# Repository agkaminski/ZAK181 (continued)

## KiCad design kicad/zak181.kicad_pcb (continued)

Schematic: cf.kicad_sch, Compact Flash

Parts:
C73: 100p; C_Disc_D5.0mm_W2.5mm_P2.50mm
D3: ACTIVITY; LED_D5.0mm
J3: Compact Flash; Conn_CF_N7E50-Q516XX-40
R19: 1K; R_Axial_DIN0207_L6.3mm_D2.5mm_P7.62mm_Horizontal
R20: 100R; R_Axial_DIN0207_L6.3mm_D2.5mm_P7.62mm_Horizontal
RN3: 1K; R_Array_SIP5

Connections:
/A0: J3.20 (A0); also elsewhere on the board
/A1: J3.19 (A1); also elsewhere on the board
/A2: J3.18 (A2); also elsewhere on the board
/D0: J3.21 (D0); also elsewhere on the board
/D1: J3.22 (D1); also elsewhere on the board
/D2: J3.23 (D2); also elsewhere on the board
/D3: J3.2 (D3); also elsewhere on the board
/D4: J3.3 (D4); also elsewhere on the board
/D5: J3.4 (D5); also elsewhere on the board
/D6: J3.5 (D6); also elsewhere on the board
/D7: J3.6 (D7); also elsewhere on the board
/cf/IRQ: J3.37 (INTRQ); also elsewhere on the board
/cf/~CS: J3.7 (~CS0); also elsewhere on the board
/cf/~RD: R20.2; also elsewhere on the board
/cf/~WR: J3.35 (~IOWR); also elsewhere on the board
/cpu/~RST: J3.41 (~RESET); also elsewhere on the board
GND: C73.2, J3.1 (GND), J3.8 (A10), J3.9 (~ATASEL), J3.10 (A9), J3.11 (A8), J3.12 (A7), J3.14 (A6), J3.15 (A5), J3.16 (A4), J3.17 (A3), J3.39 (~CSEL), J3.50 (GND); also elsewhere on the board
unnamed: D3.2 (A), R19.1
unnamed: D3.1 (K), J3.45 (~DASP)
unnamed: J3.32 (~CS1), RN3.5 (R4)
unnamed: C73.1, J3.34 (~IORD), R20.1
unnamed: J3.46 (~PDIAG), RN3.2 (R1)
unnamed: J3.44 (~REG), RN3.4 (R3)
unnamed: J3.36 (~WE), RN3.3 (R2)
VCC: J3.13 (VCC), J3.38 (VCC), R19.2, RN3.1 (common); also elsewhere on the board

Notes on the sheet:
Regarding CF slot footprint: Market is a proper mess. These cards seem to be obsolete and everything is hard to aquire. Footprint used fits somewhat avaiable CF-50P - normal order, not reversed! Card has to be label up when inserted!

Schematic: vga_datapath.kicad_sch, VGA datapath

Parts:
C4, C5, C6, C7, C8, C9, C10, C11, C12, C13: 100n; C_Disc_D5.0mm_W2.5mm_P2.50mm
Q3, Q4, Q5: BC547; TO-92
R6, R11, R14: 390R; R_Axial_DIN0207_L6.3mm_D2.5mm_P7.62mm_Horizontal
R7, R8, R9, R10, R12, R13: 3K3; R_Axial_DIN0207_L6.3mm_D2.5mm_P7.62mm_Horizontal
U21, U30: 74HC377; DIP-20_W7.62mm
U23: 27C64; DIP-28_W15.24mm
U24: 74HC166; DIP-16_W7.62mm
U27: 62256; DIP-28_W15.24mm
U32: 74HC157; DIP-16_W7.62mm

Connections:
/sound/ROMSEL0: U23.23 (A11); also elsewhere on the board
/sound/ROMSEL1: U23.2 (A12); also elsewhere on the board
/vga/BLANK: U32.15 (E); also elsewhere on the board
/vga/PCLK: U21.11 (CP), U24.7 (Clk), U30.11 (CP); also elsewhere on the board
/vga/VA0: U27.10 (A0); also elsewhere on the board
/vga/VA1: U27.9 (A1); also elsewhere on the board
/vga/VA2: U27.8 (A2); also elsewhere on the board
/vga/VA3: U27.7 (A3); also elsewhere on the board
/vga/VA4: U27.6 (A4); also elsewhere on the board
/vga/VA5: U27.5 (A5); also elsewhere on the board
/vga/VA6: U27.4 (A6); also elsewhere on the board
/vga/VA7: U27.3 (A7); also elsewhere on the board
/vga/VA8: U27.25 (A8); also elsewhere on the board
/vga/VA9: U27.24 (A9); also elsewhere on the board
/vga/VA10: U27.21 (A10); also elsewhere on the board
/vga/VA11: U27.23 (A11); also elsewhere on the board
/vga/VA12: U27.2 (A12); also elsewhere on the board
/vga/VA13: U27.26 (A13); also elsewhere on the board
/vga/VD0: U21.3 (D0), U27.11 (Q0), U30.3 (D0); also elsewhere on the board
/vga/VD1: U21.4 (D1), U27.12 (Q1), U30.4 (D1); also elsewhere on the board
/vga/VD2: U21.7 (D2), U27.13 (Q2), U30.7 (D2); also elsewhere on the board
/vga/VD3: U21.8 (D3), U27.15 (Q3), U30.8 (D3); also elsewhere on the board
/vga/VD4: U21.13 (D4), U27.16 (Q4), U30.13 (D4); also elsewhere on the board
/vga/VD5: U21.14 (D5), U27.17 (Q5), U30.14 (D5); also elsewhere on the board
/vga/VD6: U21.17 (D6), U27.18 (Q6), U30.17 (D6); also elsewhere on the board
/vga/VD7: U21.18 (D7), U27.19 (Q7), U30.18 (D7); also elsewhere on the board
/vga/vga_datapath/BLUE: R14.2; also elsewhere on the board
/vga/vga_datapath/CROW0: U23.10 (A0); also elsewhere on the board
/vga/vga_datapath/CROW1: U23.9 (A1); also elsewhere on the board
/vga/vga_datapath/CROW2: U23.8 (A2); also elsewhere on the board
/vga/vga_datapath/GREEN: R11.2; also elsewhere on the board
/vga/vga_datapath/RED: R6.2; also elsewhere on the board
/vga/~CLOAD: U30.1 (~E); also elsewhere on the board
/vga/~PLOAD: U21.1 (~E); also elsewhere on the board
/vga/~SHLOAD: U24.15 (PE); also elsewhere on the board
/vga/~VOE: U27.22 (~OE); also elsewhere on the board
/vga/~VWE: U27.27 (~WE); also elsewhere on the board
GND: C4.2, C5.2, C6.2, C7.2, C8.2, C9.2, C10.2, C11.2, C12.2, C13.2, U21.10 (GND), U23.14 (GND), U23.20 (~CE), U23.22 (~OE), U24.1 (Ds), U24.6 (CE), U24.8 (GND), U27.1 (A14), U27.14 (GND), U27.20 (~CS), U30.10 (GND), U32.8 (GND); also elsewhere on the board
unnamed: Q3.2 (B), R7.2, R8.2
unnamed: Q3.3 (E), R6.1
unnamed: Q4.2 (B), R9.2, R10.2
unnamed: Q4.3 (E), R11.1
unnamed: Q5.2 (B), R12.2, R13.2
unnamed: Q5.3 (E), R14.1
unnamed: U21.2 (Q0), U23.7 (A3)
unnamed: U21.5 (Q1), U23.6 (A4)
unnamed: U21.6 (Q2), U23.5 (A5)
unnamed: U21.9 (Q3), U23.4 (A6)
unnamed: U21.12 (Q4), U23.3 (A7)
unnamed: U21.15 (Q5), U23.25 (A8)
unnamed: U21.16 (Q6), U23.24 (A9)
unnamed: U21.19 (Q7), U23.21 (A10)
unnamed: U23.11 (D0), U24.2 (A)
unnamed: U23.12 (D1), U24.3 (B)
unnamed: U23.13 (D2), U24.4 (C)
unnamed: U23.15 (D3), U24.5 (D)
unnamed: U23.16 (D4), U24.10 (E)
unnamed: U23.17 (D5), U24.11 (F)
unnamed: U23.18 (D6), U24.12 (G)
unnamed: U23.19 (D7), U24.14 (H)
unnamed: U24.13 (Qh), U32.1 (S)
unnamed: U30.2 (Q0), U32.2 (I0a)
unnamed: U30.5 (Q1), U32.5 (I0b)
unnamed: U30.6 (Q2), U32.11 (I0c)
unnamed: U30.9 (Q3), U32.14 (I0d)
unnamed: U30.12 (Q4), U32.3 (I1a)
unnamed: U30.15 (Q5), U32.6 (I1b)
unnamed: U30.16 (Q6), U32.10 (I1c)
unnamed: U30.19 (Q7), U32.13 (I1d)
unnamed: R7.1, U32.4 (Za)
unnamed: R9.1, U32.7 (Zb)
unnamed: R12.1, U32.9 (Zc)
unnamed: R8.1, R10.1, R13.1, U32.12 (Zd)
VCC: C4.1, C5.1, C6.1, C7.1, C8.1, C9.1, C10.1, C11.1, C12.1, C13.1, Q3.1 (C), Q4.1 (C), Q5.1 (C), U21.20 (VCC), U23.1 (VPP), U23.27 (~PGM), U23.28 (VCC), U24.9 (Clr), U24.16 (VCC), U27.28 (VCC), U30.20 (VCC), U32.16 (VCC); also elsewhere on the board

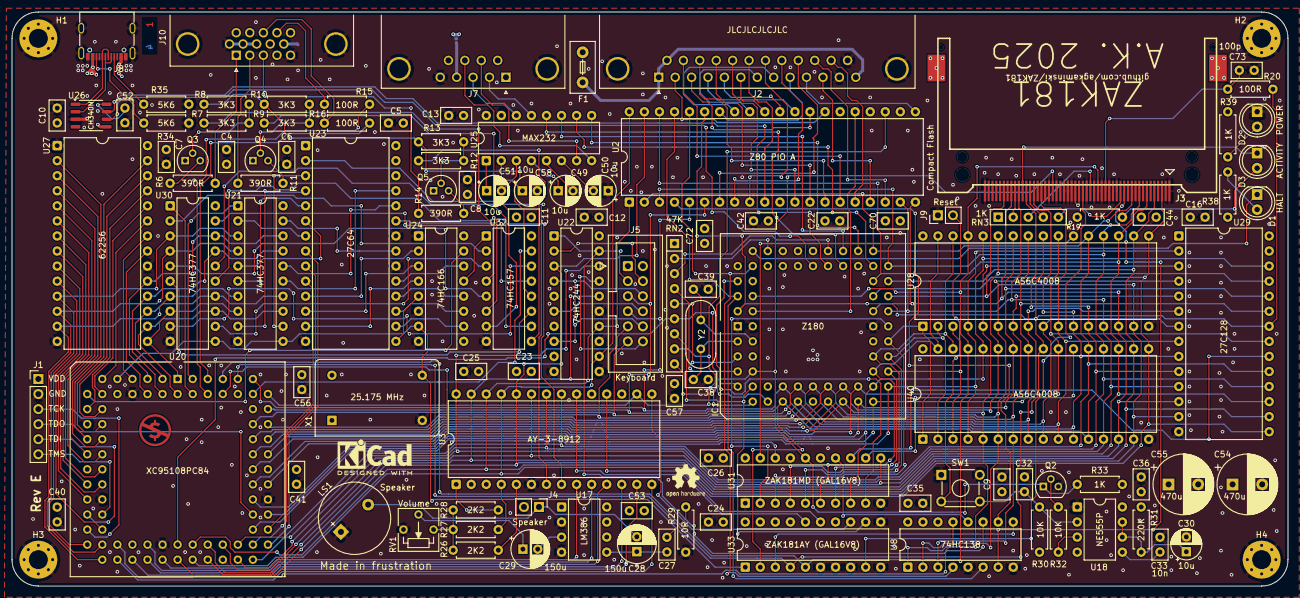
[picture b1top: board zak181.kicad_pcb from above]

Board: 4 copper layers, 215.3 x 96.8 mm, 118 parts (1 on the bottom side), 219 nets.

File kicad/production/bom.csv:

Designator,Footprint,Quantity,Value,LCSC Part #
"C10, C11, C12, C13, C16, C22, C23, C24, C25, C26, C32, C35, C36, C4, C40, C41, C42, C44, C5, C52, C53, C56, C57, C6, C7, C70, C72, C8, C9",C_Disc_D5.0mm_W2.5mm_P2.50mm,29,100n,
C27,C_Disc_D5.0mm_W2.5mm_P2.50mm,1,47n,
"C28, C29",CP_Radial_D6.3mm_P2.50mm,2,150u,
"C30, C49, C50, C51, C58",CP_Radial_D5.0mm_P2.50mm,5,10u,
C33,C_Disc_D5.0mm_W2.5mm_P2.50mm,1,10n,
"C38, C39",C_Disc_D5.0mm_W2.5mm_P2.50mm,2,22p,
"C54, C55",CP_Radial_D10.0mm_P5.00mm,2,470u,
C73,C_Disc_D5.0mm_W2.5mm_P2.50mm,1,100p,
D1,LED_D5.0mm,1,HALT,
D2,LED_D5.0mm,1,POWER,
D3,LED_D5.0mm,1,ACTIVITY,
F1,Fuse_Littelfuse_395Series,1,Fuse,
IC1,PLCC-68_THT-Socket,1,Z180,
J1,PinHeader_1x06_P2.54mm_Vertical,1,JTAG,
J10,DSUB-15-HD_Socket_Horizontal_P2.29x1.90mm_EdgePinOffset3.03mm_Housed_MountingHolesOffset4.94mm,1,DE15,
J2,DSUB-25_Socket_Horizontal_P2.77x2.84mm_EdgePinOffset7.70mm_Housed_MountingHolesOffset9.12mm,1,DB25_Receptacle_MountingHoles,
J3,Conn_CF_N7E50-Q516XX-40,1,Compact Flash,
J4,PinHeader_1x02_P2.54mm_Vertical,1,Speaker,
J5,IDC-Header_2x06_P2.54mm_Vertical,1,Keyboard,
J7,DSUB-9_Pins_Horizontal_P2.77x2.84mm_EdgePinOffset7.70mm_Housed_MountingHolesOffset9.12mm,1,DSUB-9,
J8,USB_C_Receptacle_G-Switch_GT-USB-7010ASV,1,USB C,
J9,PinHeader_1x02_P2.54mm_Vertical,1,Reset,
JP1,SolderJumper-2_P1.3mm_Bridged_Pad1.0x1.5mm,1,Jumper_2_Bridged,
LS1,MagneticBuzzer_StarMicronics_QMB-105,1,Speaker,
"Q2, Q3, Q4, Q5",TO-92,4,BC547,
"R10, R12, R13, R7, R8, R9",R_Axial_DIN0207_L6.3mm_D2.5mm_P7.62mm_Horizontal,6,3K3,
"R11, R14, R6",R_Axial_DIN0207_L6.3mm_D2.5mm_P7.62mm_Horizontal,3,390R,
"R15, R16, R20",R_Axial_DIN0207_L6.3mm_D2.5mm_P7.62mm_Horizontal,3,100R,
"R19, R33, R38, R39",R_Axial_DIN0207_L6.3mm_D2.5mm_P7.62mm_Horizontal,4,1K,
"R26, R27, R28",R_Axial_DIN0207_L6.3mm_D2.5mm_P7.62mm_Horizontal,3,2K2,
R29,R_Axial_DIN0207_L6.3mm_D2.5mm_P7.62mm_Horizontal,1,10R,
"R30, R32",R_Axial_DIN0207_L6.3mm_D2.5mm_P7.62mm_Horizontal,2,10K,
R31,R_Axial_DIN0207_L6.3mm_D2.5mm_P7.62mm_Horizontal,1,220K,
"R34, R35",R_Axial_DIN0207_L6.3mm_D2.5mm_P7.62mm_Horizontal,2,5K6,
RN2,R_Array_SIP9,1,47K,
RN3,R_Array_SIP5,1,1K,
RV1,Potentiometer_Vishay_T73YP_Vertical,1,1K,
SW1,SW_TH_Tactile_Omron_B3F-10xx,1,Reset,
U17,DIP-8_W7.62mm,1,LM386,
U18,DIP-8_W7.62mm,1,NE555P,
U2,DIP-40_W15.24mm,1,Z80 PIO A,
U20,PLCC-84_THT-Socket,1,XC95108PC84,
"U21, U30",DIP-20_W7.62mm,2,74HC377,
U22,DIP-20_W7.62mm,1,74HC244,
U23,DIP-28_W15.24mm,1,27C64,
U24,DIP-16_W7.62mm,1,74HC166,
U25,DIP-16_W7.62mm,1,MAX232,
U26,SOP-8_3.9x4.9mm_P1.27mm,1,CH340N,
U27,DIP-28_W15.24mm,1,62256,
"U28, U40",DIP-32_W15.24mm,2,AS6C4008,
U29,DIP-28_W15.24mm,1,27C128,
U3,DIP-28_W15.24mm,1,AY-3-8912,
U31,DIP-20_W7.62mm,1,ZAK181MD (GAL16V8),
U32,DIP-16_W7.62mm,1,74HC157,
U33,DIP-20_W7.62mm,1,ZAK181AY (GAL16V8),
U8,DIP-16_W7.62mm,1,74HC138,
X1,Oscillator_DIP-14,1,25.175 MHz,
Y2,Crystal_HC49-4H_Vertical,1,12.288 MHz,

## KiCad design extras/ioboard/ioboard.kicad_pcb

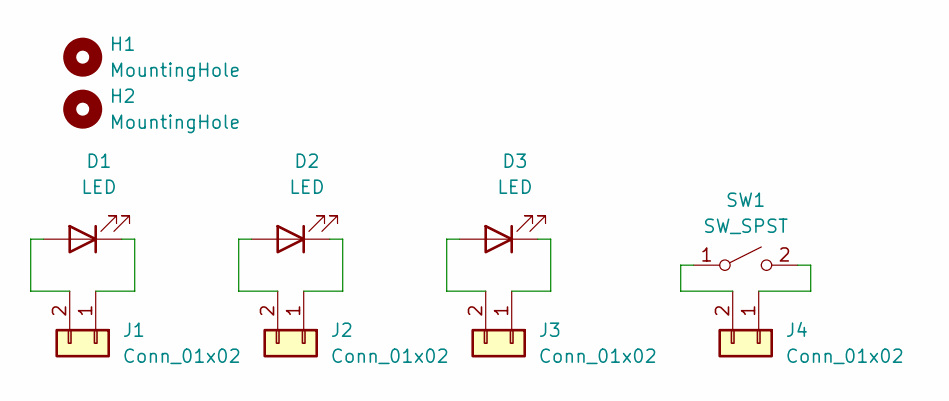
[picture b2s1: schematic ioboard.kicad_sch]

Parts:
D1, D2, D3: LED; LED_D5.0mm
H1, H2: MountingHole; MountingHole_3.2mm_M3_Pad_Via
J1, J2, J3, J4: Conn_01x02; PinHeader_1x02_P2.54mm_Vertical
SW1: SW_SPST; SW_PUSH_6mm

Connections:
unnamed: D1.2 (A), J1.2
unnamed: D1.1 (K), J1.1
unnamed: D2.2 (A), J2.2
unnamed: D2.1 (K), J2.1
unnamed: D3.2 (A), J3.2
unnamed: D3.1 (K), J3.1
unnamed: J4.1, SW1.2 (B)
unnamed: J4.2, SW1.1 (A)

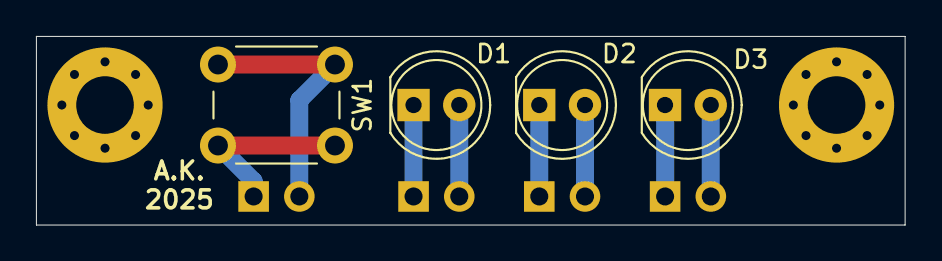
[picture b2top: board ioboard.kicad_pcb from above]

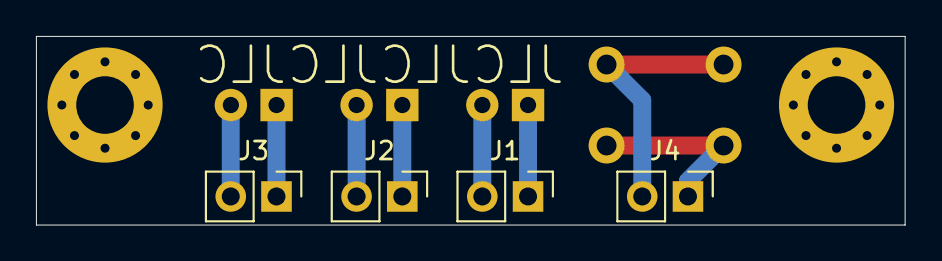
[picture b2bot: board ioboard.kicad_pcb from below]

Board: 2 copper layers, 48.3 x 10.5 mm, 10 parts (4 on the bottom side), 8 nets.

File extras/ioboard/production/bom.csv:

Designator,Footprint,Quantity,Value,LCSC Part #
"D1, D2, D3",LED_D5.0mm,3,LED,
"J1, J2, J3, J4",PinHeader_1x02_P2.54mm_Vertical,4,Conn_01x02,
SW1,SW_PUSH_6mm,1,SW_SPST,

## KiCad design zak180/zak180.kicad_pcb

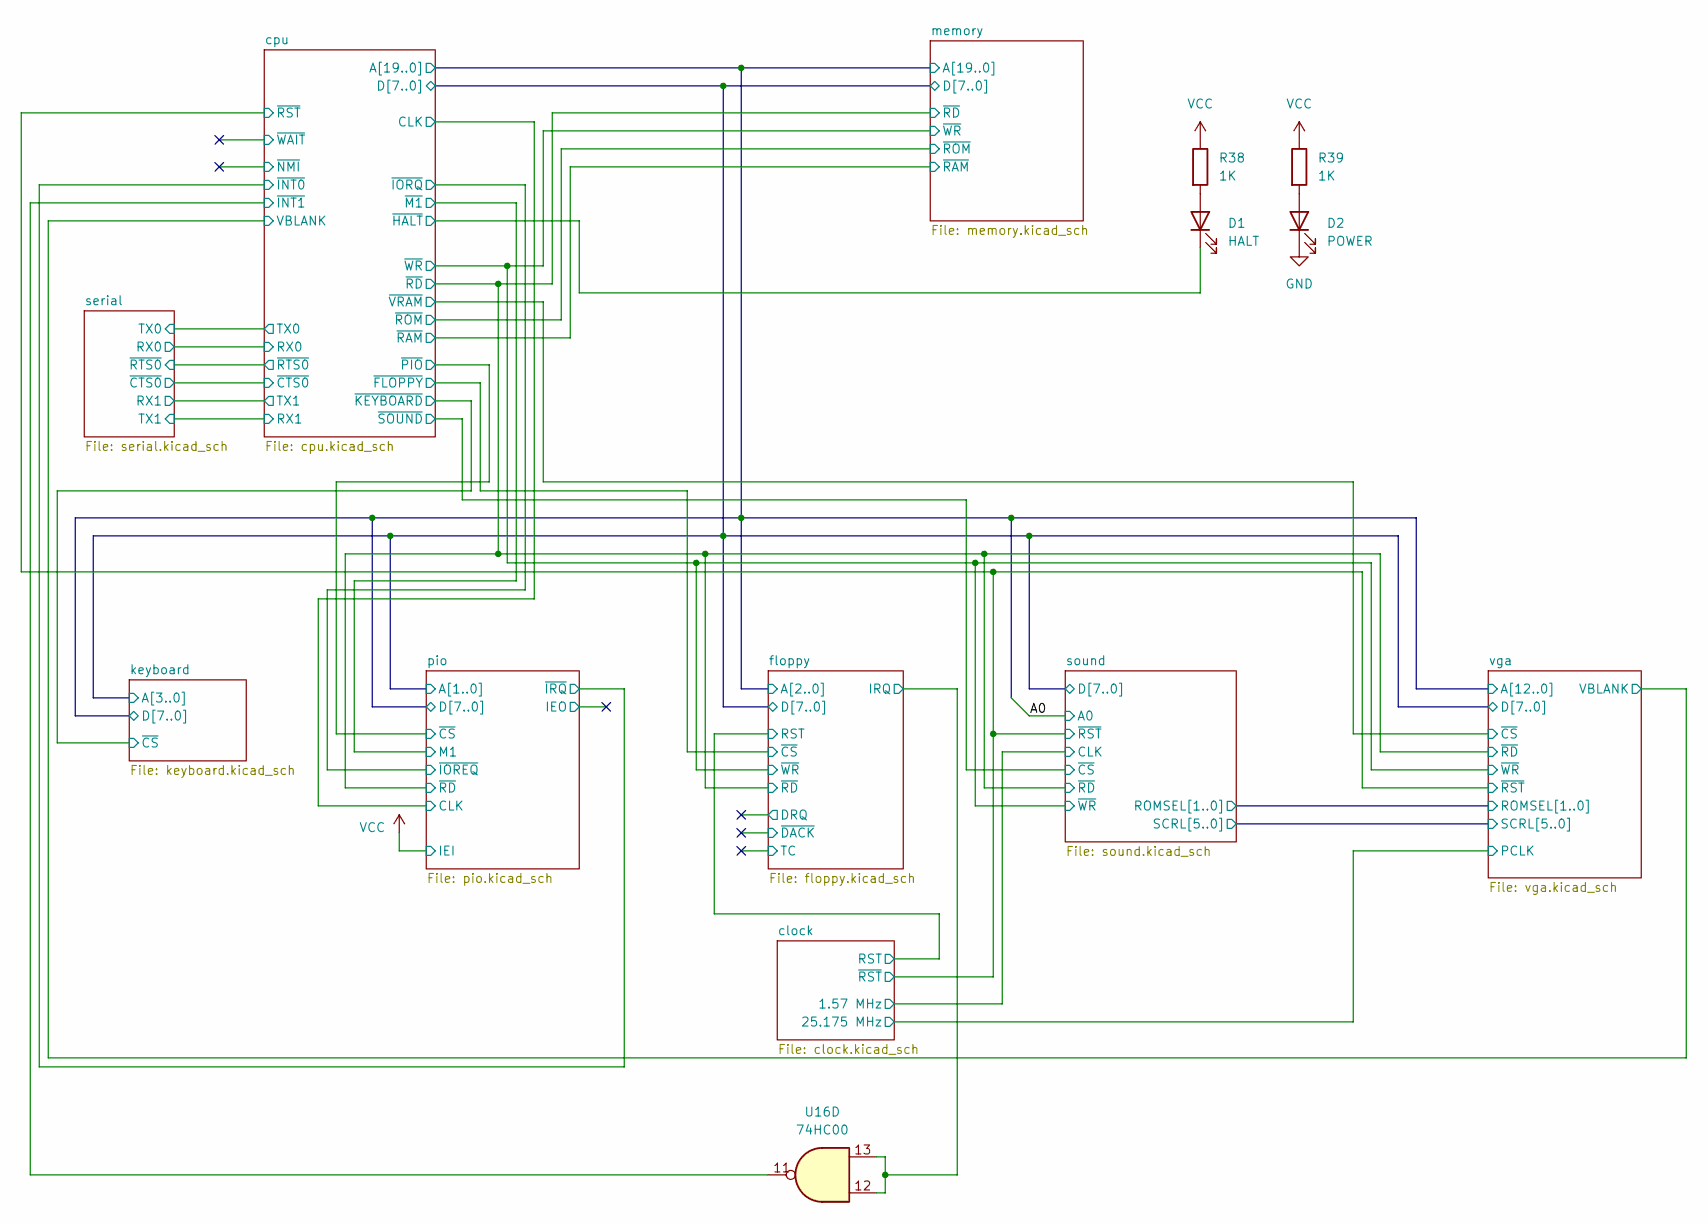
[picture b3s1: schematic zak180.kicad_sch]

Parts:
D1: HALT; LED_D5.0mm
D2: POWER; LED_D5.0mm
R38, R39: 1K; R_Axial_DIN0207_L6.3mm_D2.5mm_P7.62mm_Horizontal
U16: 74HC00; DIP-14_W7.62mm

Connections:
/cpu/~HALT: D1.1 (K); also elsewhere on the board
/cpu/~INT1: U16.11; also elsewhere on the board
/floppy/IRQ: U16.12, U16.13; also elsewhere on the board
GND: D2.1 (K); also elsewhere on the board
unnamed: D1.2 (A), R38.2
unnamed: D2.2 (A), R39.2
VCC: R38.1, R39.1; also elsewhere on the board

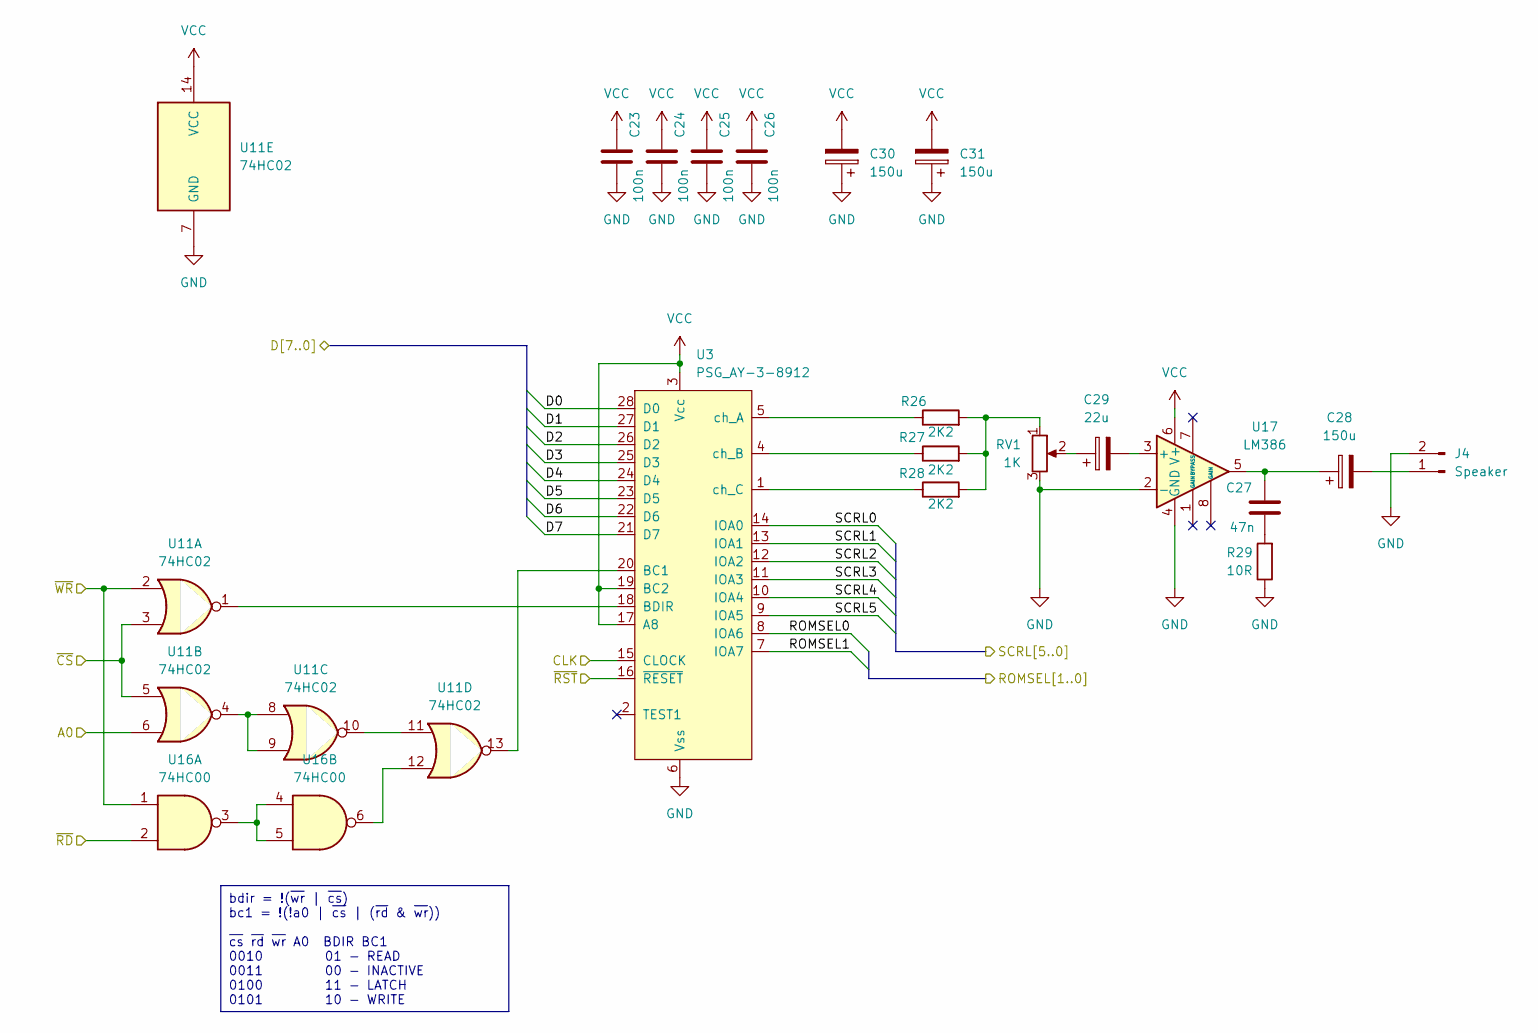
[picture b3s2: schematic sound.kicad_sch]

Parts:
C23, C24, C25, C26: 100n; C_Disc_D5.0mm_W2.5mm_P2.50mm
C27: 47n; C_Disc_D5.0mm_W2.5mm_P2.50mm
C28, C30, C31: 150u; CP_Radial_D10.0mm_P5.00mm
C29: 22u; CP_Radial_D10.0mm_P5.00mm
J4: Speaker; PinHeader_1x02_P1.00mm_Vertical
R26, R27, R28: 2K2; R_Axial_DIN0207_L6.3mm_D2.5mm_P7.62mm_Horizontal
R29: 10R; R_Axial_DIN0207_L6.3mm_D2.5mm_P7.62mm_Horizontal
RV1: 1K; Potentiometer_Vishay_T73YP_Vertical
U3: PSG_AY-3-8912; DIP-28_W15.24mm
U11: 74HC02; DIP-14_W7.62mm
U16: 74HC00; DIP-14_W7.62mm
U17: LM386; DIP-8_W7.62mm

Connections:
/clock/1.57 MHz: U3.15 (CLOCK); also elsewhere on the board
/clock/~RST: U3.16 (~RESET); also elsewhere on the board
/cpu/D0: U3.28 (D0), U11.6; also elsewhere on the board
/cpu/D1: U3.27 (D1); also elsewhere on the board
/cpu/D2: U3.26 (D2); also elsewhere on the board
/cpu/D3: U3.25 (D3); also elsewhere on the board
/cpu/D4: U3.24 (D4); also elsewhere on the board
/cpu/D5: U3.23 (D5); also elsewhere on the board
/cpu/D6: U3.22 (D6); also elsewhere on the board
/cpu/D7: U3.21 (D7); also elsewhere on the board
/cpu/~RD: U16.2; also elsewhere on the board
/cpu/~SOUND: U11.3, U11.5; also elsewhere on the board
/cpu/~WR: U11.2, U16.1; also elsewhere on the board
/sound/ROMSEL0: U3.8 (IOA6); also elsewhere on the board
/sound/ROMSEL1: U3.7 (IOA7); also elsewhere on the board
/sound/SCRL0: U3.14 (IOA0); also elsewhere on the board
/sound/SCRL1: U3.13 (IOA1); also elsewhere on the board
/sound/SCRL2: U3.12 (IOA2); also elsewhere on the board
/sound/SCRL3: U3.11 (IOA3); also elsewhere on the board
/sound/SCRL4: U3.10 (IOA4); also elsewhere on the board
/sound/SCRL5: U3.9 (IOA5); also elsewhere on the board
GND: C23.2, C24.2, C25.2, C26.2, C30.1, C31.1, J4.2, R29.1, RV1.3, U3.6 (Vss), U11.7 (GND), U17.2 (-), U17.4 (GND); also elsewhere on the board
unnamed: C27.1, C28.1, U17.5
unnamed: C27.2, R29.2
unnamed: C29.1, RV1.2
unnamed: C28.2, J4.1
unnamed: R26.2, R27.2, R28.2, RV1.1
unnamed: U3.20 (BC1), U11.13
unnamed: U3.18 (BDIR), U11.1
unnamed: R26.1, U3.5 (ch_A)
unnamed: R27.1, U3.4 (ch_B)
unnamed: R28.1, U3.1 (ch_C)
unnamed: U11.4, U11.8, U11.9
unnamed: U11.10, U11.11
unnamed: U11.12, U16.6
unnamed: U16.3, U16.4, U16.5
unnamed: C29.2, U17.3 (+)
VCC: C23.1, C24.1, C25.1, C26.1, C30.2, C31.2, U3.3 (Vcc), U3.17 (A8), U3.19 (BC2), U11.14 (VCC), U17.6 (V+); also elsewhere on the board

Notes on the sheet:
bdir = !(~{wr} | ~{cs}) bc1 = !(!a0 | ~{cs} | (~{rd} & ~{wr})) ~{cs} ~{rd} ~{wr} A0 BDIR BC1 0010 01 - READ 0011 00 - INACTIVE 0100 11 - LATCH 0101 10 - WRITE

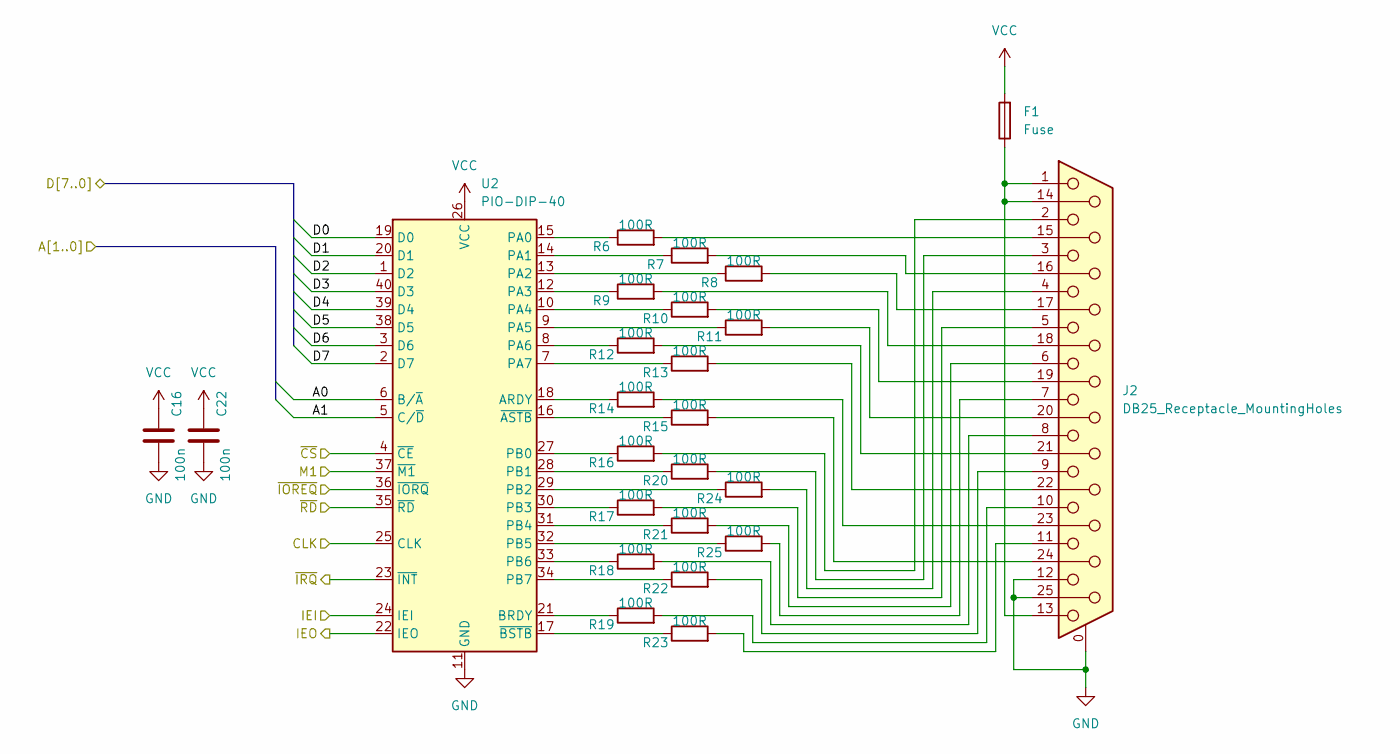
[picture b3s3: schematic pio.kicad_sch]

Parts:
C16, C22: 100n; C_Disc_D5.0mm_W2.5mm_P2.50mm
F1: Fuse; Fuse_Littelfuse_395Series
J2: DB25_Receptacle_MountingHoles; DSUB-25_Female_Horizontal_P2.77x2.84mm_EdgePinOffset9.90mm_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
R6, R7, R8, R9, R10, R11, R12, R13, R14, R15, R16, R17, R18, R19, R20, R21, R22, R23, R24, R25: 100R; R_Axial_DIN0207_L6.3mm_D2.5mm_P7.62mm_Horizontal
U2: PIO-DIP-40; DIP-40_W15.24mm

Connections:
/cpu/A0: U2.19 (D0); also elsewhere on the board
/cpu/A1: U2.20 (D1); also elsewhere on the board
/cpu/A2: U2.1 (D2); also elsewhere on the board
/cpu/A3: U2.40 (D3); also elsewhere on the board
/cpu/A4: U2.39 (D4); also elsewhere on the board
/cpu/A5: U2.38 (D5); also elsewhere on the board
/cpu/A6: U2.3 (D6); also elsewhere on the board
/cpu/A7: U2.2 (D7); also elsewhere on the board
/cpu/CLK: U2.25 (CLK); also elsewhere on the board
/cpu/D0: U2.6 (B/~A); also elsewhere on the board
/cpu/D1: U2.5 (C/~D); also elsewhere on the board
/cpu/~INT0: U2.23 (~INT); also elsewhere on the board
/cpu/~IORQ: U2.36 (~IORQ); also elsewhere on the board
/cpu/~M1: U2.37 (~M1); also elsewhere on the board
/cpu/~PIO: U2.4 (~CE); also elsewhere on the board
/cpu/~RD: U2.35 (~RD); also elsewhere on the board
/pio/IEO: U2.22 (IEO)
GND: C16.2, C22.2, J2.0 (PAD), J2.12, J2.25, U2.11 (GND); also elsewhere on the board
unnamed: F1.1, J2.1, J2.13, J2.14
unnamed: J2.15, R6.2
unnamed: J2.16, R7.2
unnamed: J2.17, R8.2
unnamed: J2.18, R9.2
unnamed: J2.19, R10.2
unnamed: J2.20, R11.2
unnamed: J2.21, R12.2
unnamed: J2.22, R13.2
unnamed: J2.23, R14.2
unnamed: J2.24, R15.2
unnamed: J2.2, R16.2
unnamed: J2.3, R20.2
unnamed: J2.4, R24.2
unnamed: J2.5, R17.2
unnamed: J2.6, R21.2
unnamed: J2.7, R25.2
unnamed: J2.8, R18.2
unnamed: J2.9, R22.2
unnamed: J2.10, R19.2
unnamed: J2.11, R23.2
unnamed: R14.1, U2.18 (ARDY)
unnamed: R19.1, U2.21 (BRDY)
unnamed: R6.1, U2.15 (PA0)
unnamed: R7.1, U2.14 (PA1)
unnamed: R8.1, U2.13 (PA2)
unnamed: R9.1, U2.12 (PA3)
unnamed: R10.1, U2.10 (PA4)
unnamed: R11.1, U2.9 (PA5)
unnamed: R12.1, U2.8 (PA6)
unnamed: R13.1, U2.7 (PA7)
unnamed: R16.1, U2.27 (PB0)
unnamed: R20.1, U2.28 (PB1)
unnamed: R24.1, U2.29 (PB2)
unnamed: R17.1, U2.30 (PB3)
unnamed: R21.1, U2.31 (PB4)
unnamed: R25.1, U2.32 (PB5)
unnamed: R18.1, U2.33 (PB6)
unnamed: R22.1, U2.34 (PB7)
unnamed: R15.1, U2.16 (~ASTB)
unnamed: R23.1, U2.17 (~BSTB)
VCC: C16.1, C22.1, F1.2, U2.24 (IEI), U2.26 (VCC); also elsewhere on the board

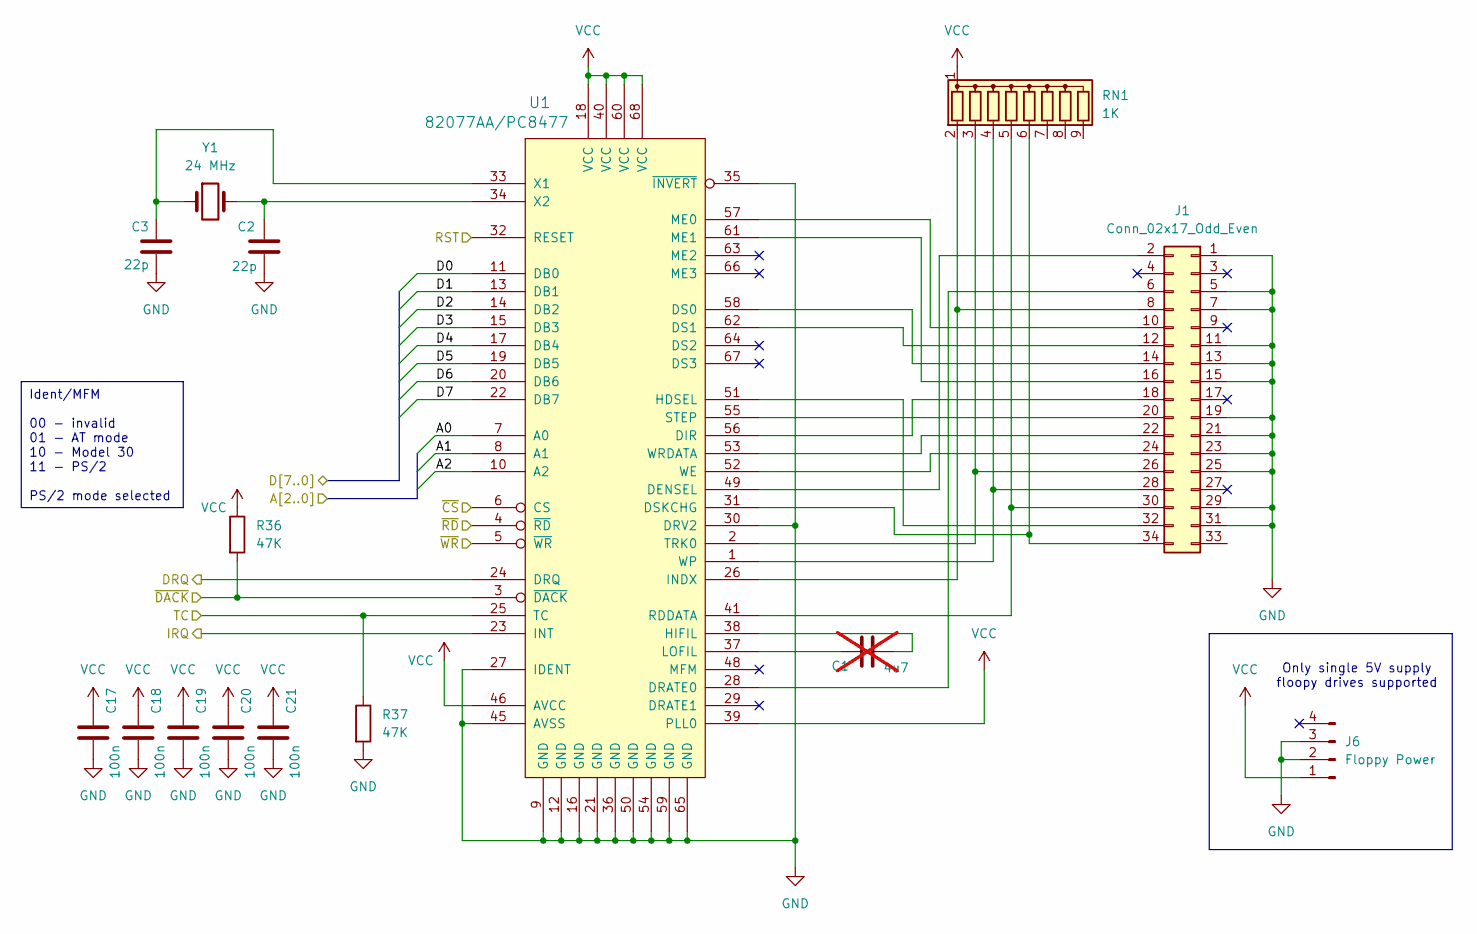
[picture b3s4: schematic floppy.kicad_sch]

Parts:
C1: 4u7; C_Disc_D4.3mm_W1.9mm_P5.00mm; not fitted
C2, C3: 22p; C_Disc_D4.3mm_W1.9mm_P5.00mm
C17, C18, C19, C20, C21: 100n; C_Disc_D5.0mm_W2.5mm_P2.50mm
J1: Conn_02x17_Odd_Even; IDC-Header_2x17_P2.54mm_Vertical
J6: Floppy Power; PinHeader_1x04_P2.54mm_Horizontal
R36, R37: 47K; R_Axial_DIN0207_L6.3mm_D2.5mm_P7.62mm_Horizontal
RN1: 1K; R_Array_SIP9
U1: 82077AA/PC8477; PLCC-68_THT-Socket
Y1: 24 MHz; Crystal_HC49-4H_Vertical

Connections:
/clock/RST: U1.32 (RESET); also elsewhere on the board
/cpu/A0: U1.7 (A0); also elsewhere on the board
/cpu/A1: U1.8 (A1); also elsewhere on the board
/cpu/A2: U1.10 (A2); also elsewhere on the board
/cpu/D0: U1.11 (DB0); also elsewhere on the board
/cpu/D1: U1.13 (DB1); also elsewhere on the board
/cpu/D2: U1.14 (DB2); also elsewhere on the board
/cpu/D3: U1.15 (DB3); also elsewhere on the board
/cpu/D4: U1.17 (DB4); also elsewhere on the board
/cpu/D5: U1.19 (DB5); also elsewhere on the board
/cpu/D6: U1.20 (DB6); also elsewhere on the board
/cpu/D7: U1.22 (DB7); also elsewhere on the board
/cpu/~FLOPPY: U1.6 (CS); also elsewhere on the board
/cpu/~RD: U1.4 (~RD); also elsewhere on the board
/cpu/~WR: U1.5 (~WR); also elsewhere on the board
/floppy/DRQ: U1.24 (DRQ)
/floppy/IRQ: U1.23 (INT); also elsewhere on the board
/floppy/TC: R37.1, U1.25 (TC)
/floppy/~DACK: R36.2, U1.3 (~DACK)
GND: C2.1, C3.1, C17.2, C18.2, C19.2, C20.2, C21.2, J1.1, J1.5, J1.7, J1.11, J1.13, J1.15, J1.19, J1.21, J1.23, J1.25, J1.29, J1.31, J6.2, J6.3, R37.2, U1.9 (GND), U1.12 (GND), U1.16 (GND), U1.21 (GND), U1.27 (IDENT), U1.30 (DRV2), U1.35 (~INVERT), U1.36 (GND), U1.45 (AVSS), U1.50 (GND), U1.54 (GND), U1.59 (GND), U1.65 (GND); also elsewhere on the board
unnamed: J1.2, U1.49 (DENSEL)
unnamed: J1.6, U1.28 (DRATE0)
unnamed: J1.8, RN1.2 (R1), U1.26 (INDX)
unnamed: J1.10, U1.57 (ME0)
unnamed: J1.12, U1.62 (DS1)
unnamed: J1.14, U1.58 (DS0)
unnamed: J1.16, U1.61 (ME1)
unnamed: J1.18, U1.56 (DIR)
unnamed: J1.20, U1.55 (STEP)
unnamed: J1.22, U1.53 (WRDATA)
unnamed: J1.24, U1.52 (WE)
unnamed: J1.26, RN1.3 (R2), U1.2 (TRK0)
unnamed: J1.28, RN1.4 (R3), U1.1 (WP)
unnamed: J1.30, RN1.5 (R4), U1.41 (RDDATA)
unnamed: J1.32, U1.51 (HDSEL)
unnamed: J1.34, RN1.6 (R5), U1.31 (DSKCHG)
unnamed: C1.2, U1.38 (HIFIL)
unnamed: C1.1, U1.37 (LOFIL)
unnamed: C3.2, U1.33 (X1), Y1.1
unnamed: C2.2, U1.34 (X2), Y1.2
VCC: C17.1, C18.1, C19.1, C20.1, C21.1, J6.1, R36.1, RN1.1 (common), U1.18 (VCC), U1.39 (PLL0), U1.40 (VCC), U1.46 (AVCC), U1.60 (VCC), U1.68 (VCC); also elsewhere on the board

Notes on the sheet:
Ident/MFM 00 - invalid 01 - AT mode 10 - Model 30 11 - PS/2 PS/2 mode selected
Only single 5V supply floopy drives supported

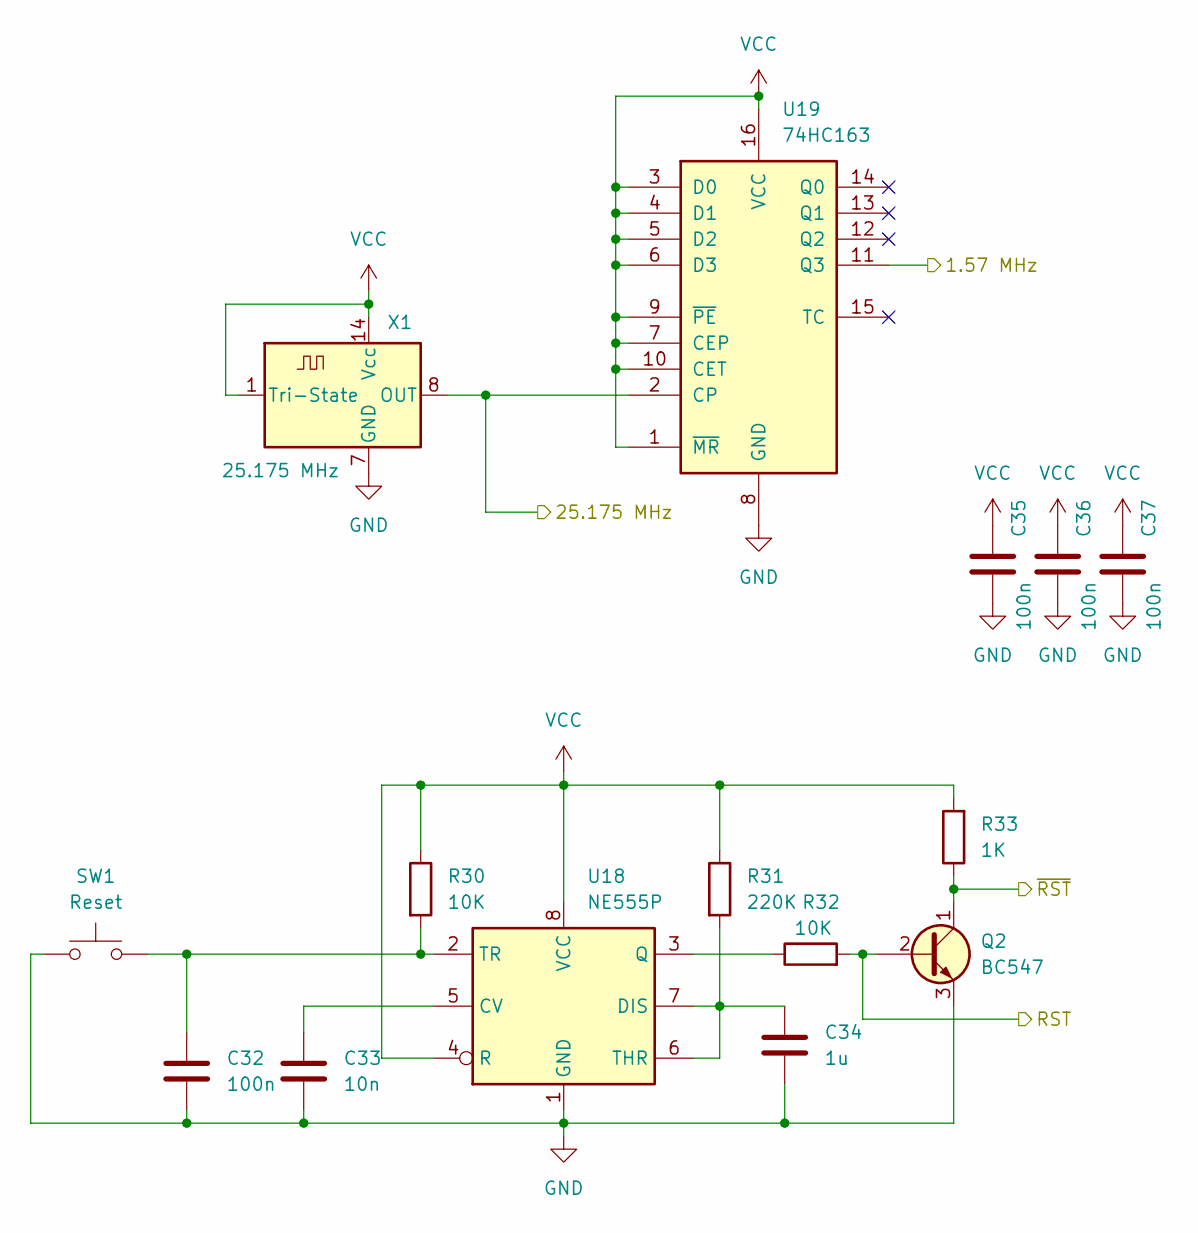
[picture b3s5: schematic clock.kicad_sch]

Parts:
C32, C35, C36, C37: 100n; C_Disc_D5.0mm_W2.5mm_P2.50mm
C33: 10n; C_Disc_D5.0mm_W2.5mm_P2.50mm
C34: 1u; C_Disc_D5.0mm_W2.5mm_P2.50mm
Q2: BC547; TO-92
R30, R32: 10K; R_Axial_DIN0207_L6.3mm_D2.5mm_P7.62mm_Horizontal
R31: 220K; R_Axial_DIN0207_L6.3mm_D2.5mm_P7.62mm_Horizontal
R33: 1K; R_Axial_DIN0207_L6.3mm_D2.5mm_P7.62mm_Horizontal
SW1: Reset; SW_TH_Tactile_Omron_B3F-10xx
U18: NE555P; DIP-8_W7.62mm
U19: 74HC163; DIP-16_W7.62mm
X1: 25.175 MHz; Oscillator_DIP-14

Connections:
/clock/1.57 MHz: U19.11 (Q3); also elsewhere on the board
/clock/25.175 MHz: U19.2 (CP), X1.8 (OUT); also elsewhere on the board
/clock/RST: Q2.2 (B), R32.2; also elsewhere on the board
/clock/~RST: Q2.1 (C), R33.1; also elsewhere on the board
GND: C32.2, C33.2, C34.2, C35.2, C36.2, C37.2, Q2.3 (E), SW1.1, U18.1 (GND), U19.8 (GND), X1.7 (GND); also elsewhere on the board
unnamed: C33.1, U18.5 (CV)
unnamed: C34.1, R31.2, U18.6 (THR), U18.7 (DIS)
unnamed: R32.1, U18.3 (Q)
unnamed: C32.1, R30.2, SW1.2, U18.2 (TR)
VCC: C35.1, C36.1, C37.1, R30.1, R31.1, R33.2, U18.4 (R), U18.8 (VCC), U19.1 (~MR), U19.3 (D0), U19.4 (D1), U19.5 (D2), U19.6 (D3), U19.7 (CEP), U19.9 (~PE), U19.10 (CET), U19.16 (VCC), X1.1 (Tri-State), X1.14 (Vcc); also elsewhere on the board
